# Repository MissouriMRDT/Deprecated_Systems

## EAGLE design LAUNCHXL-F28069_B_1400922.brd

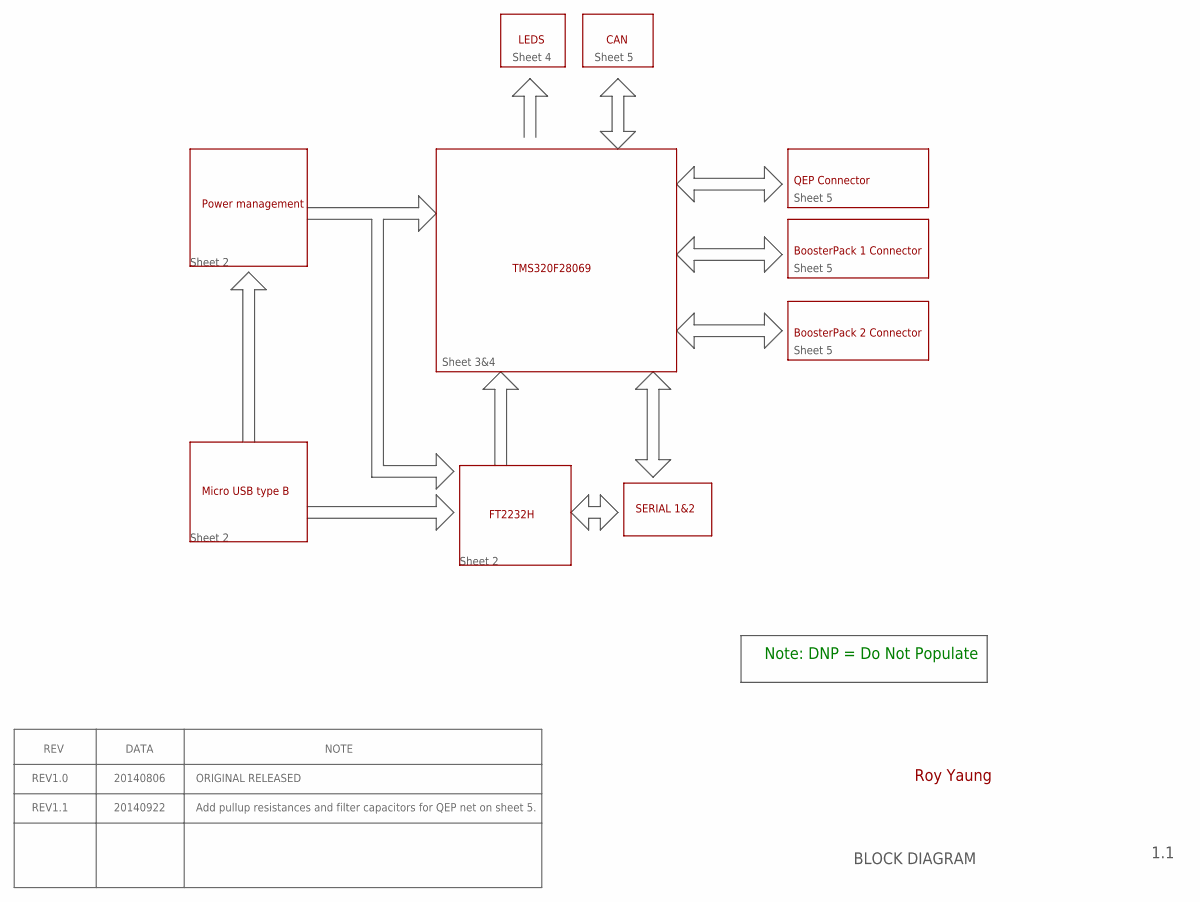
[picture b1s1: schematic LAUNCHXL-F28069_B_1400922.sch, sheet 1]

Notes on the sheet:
1.1
BLOCK DIAGRAM
Power management
Micro USB type B
FT2232H
TMS320F28069
BoosterPack 1 Connector
LEDS
CAN
SERIAL 1&2
Sheet 2
Sheet 3&4
BoosterPack 2 Connector
QEP Connector
Note: DNP = Do Not Populate
Roy Yaung
Sheet 5
Sheet 4
REV
DATA
NOTE
REV1.0
REV1.1
20140806
20140922
ORIGINAL RELEASED
Add pullup resistances and filter capacitors for QEP net on sheet 5.

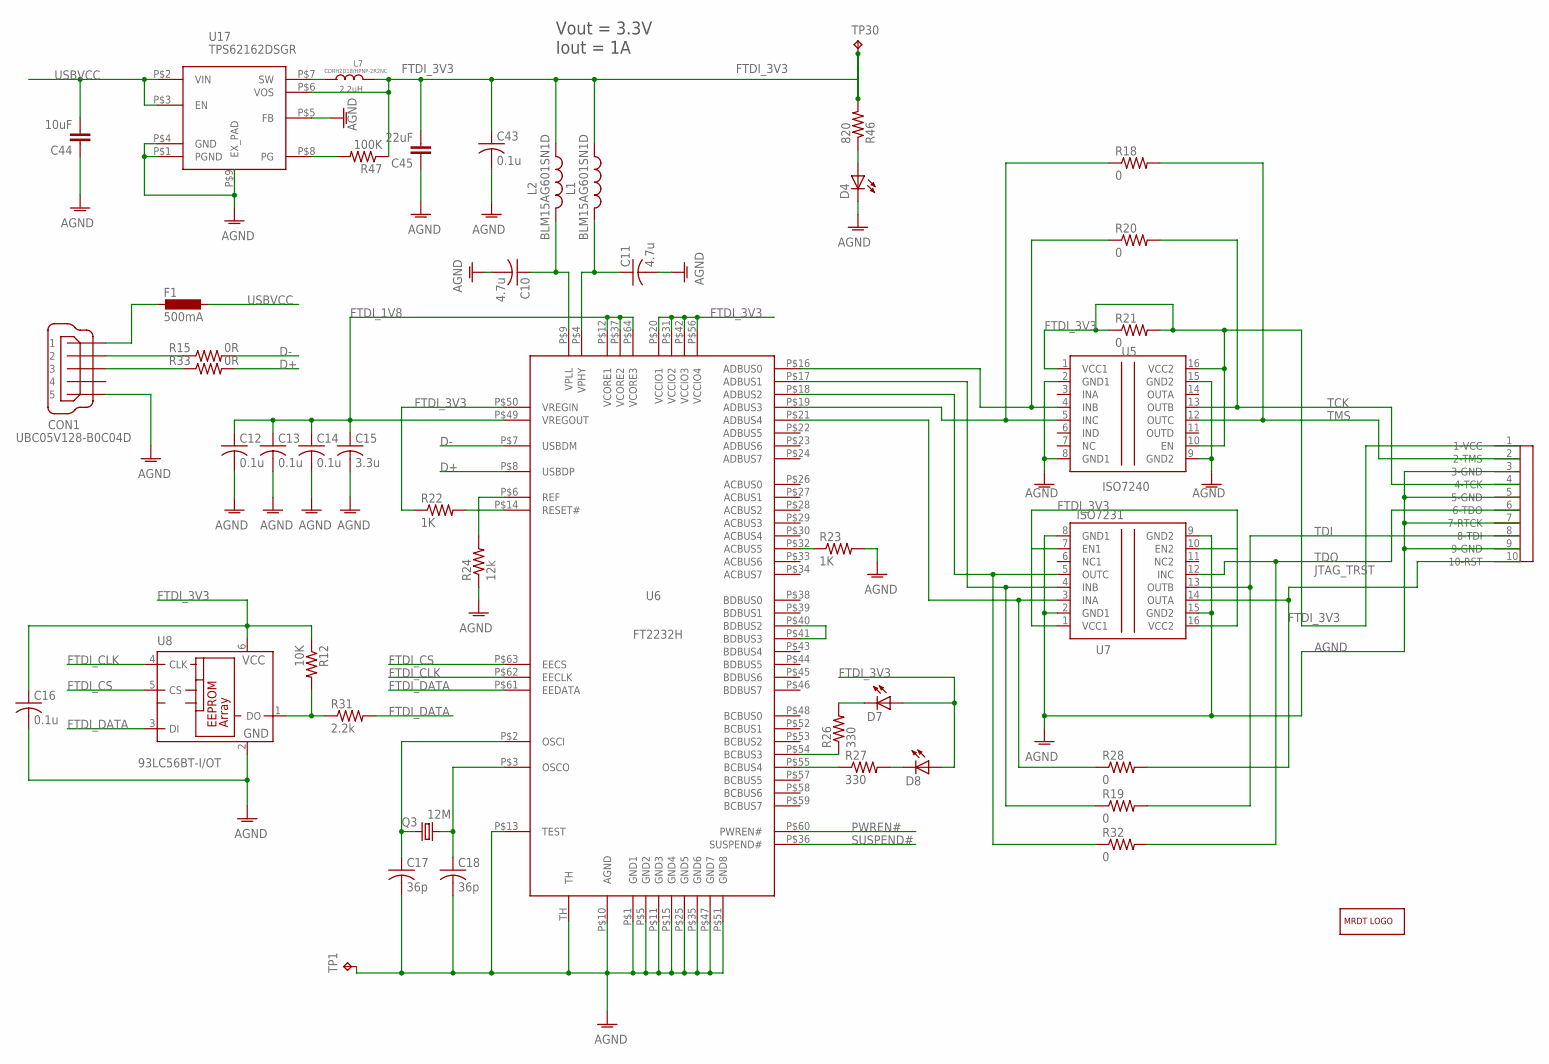
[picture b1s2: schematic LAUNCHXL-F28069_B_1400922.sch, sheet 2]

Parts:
C10, C11: 4.7u; C0402
C12, C13, C14, C16, C43: 0.1u; C0402
C15: 3.3u; C0402
C17, C18: 36p; C0402
C44: 10uF; SPARKFUN_1210
C45: 22uF; SPARKFUN_1210
CON1: UBC05V128-B0C04D; 32005-201
D4, D7, D8: LEDCHIP-LED0603; CHIP-LED0603
F1: 500mA; L1812
L1, L2: BLM15AG601SN1D; R0402
L7: 2.2uH; INDUCT-3.2*3.2
LOGO1: MRDT_LOGO
Q3: 12M; HC49UP
R12: 10K; R0402
R15, R33: 0R; R0402
R18, R19, R20, R21, R28, R32: 0; R1206
R22, R23: 1K; R0402
R24: 12k; R0402
R26, R27: 330; R0402
R31: 2.2k; R0402
R46: 820; R0402
R47: 100K; R0402
TP1, TP30: TESTPAD_TPB1,27; TESTPAD_B1,27
U5: ISO7240; SO-16DW
U6: FT2232H; QFN64
U7: ISO7231; SO-16DW
U8: 93LC56BT-I/OT; SOT23-6
U17: TPS62162DSGR; TI_DSG8
U$1: 1175-1733-ND; 1.27MM_2X5_BOX_HEADER_STRAIGHT

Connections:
AGND: C10.2, C11.2, C12.2, C13.2, C14.2, C15.2, C16.2, C17.2, C18.2, C43.2, C44.1, C45.1, CON1.5, D4.C, R23.2, R24.1, TP1.TP, U5.2 (GND1), U5.8 (GND1), U5.9 (GND2), U5.15 (GND2), U6.P$1 (GND1), U6.P$5 (GND2), U6.P$10 (AGND), U6.P$11 (GND3), U6.P$13 (TEST), U6.P$15 (GND4), U6.P$25 (GND5), U6.P$35 (GND6), U6.P$47 (GND7), U6.P$51 (GND8), U6.TH, U7.2 (GND1), U7.8 (GND1), U7.9 (GND2), U7.15 (GND2), U8.2 (GND), U17.P$1 (PGND), U17.P$4 (GND), U17.P$5 (FB), U17.P$9 (EX_PAD), U$1.3 (3-GND), U$1.5 (5-GND), U$1.7 (7-RTCK), U$1.9 (9-GND); also elsewhere on the board
D+: R33.2, U6.P$8 (USBDP)
D-: R15.2, U6.P$7 (USBDM)
FTDI_1V8: C12.1, C13.1, C14.1, C15.1, U6.P$12 (VCORE1), U6.P$37 (VCORE2), U6.P$49 (VREGOUT), U6.P$64 (VCORE3)
FTDI_3V3: C16.1, C43.1, C45.2, D7.A, D8.A, L1.1, L2.1, L7.P$1 (1), R12.1, R21.1, R21.2, R22.1, R46.2, R47.1, TP30.TP, U5.1 (VCC1), U5.10 (EN), U5.16 (VCC2), U6.P$20 (VCCIO1), U6.P$31 (VCCIO2), U6.P$42 (VCCIO3), U6.P$50 (VREGIN), U6.P$56 (VCCIO4), U7.1 (VCC1), U7.7 (EN1), U7.10 (EN2), U7.16 (VCC2), U8.6 (VCC), U17.P$6 (VOS), U$1.1 (1-VCC); also elsewhere on the board
FTDI_CLK: U6.P$62 (EECLK), U8.4 (CLK)
FTDI_CS: U6.P$63 (EECS), U8.5 (CS)
FTDI_DATA: R31.2, U6.P$61 (EEDATA), U8.3 (DI)
JTAG_TRST: R28.2, U7.14 (OUTA), U$1.10 (10-RST)
unnamed: R20.1, U5.4 (INB), U6.P$16 (ADBUS0)
unnamed: C17.1, Q3.1, U6.P$2 (OSCI)
unnamed: R19.1, U6.P$17 (ADBUS1), U7.4 (INB)
unnamed: R32.1, U6.P$18 (ADBUS2), U7.5 (OUTC)
unnamed: R18.1, U5.5 (INC), U6.P$19 (ADBUS3)
unnamed: C18.1, Q3.2, U6.P$3 (OSCO)
unnamed: R12.2, R31.1, U8.1 (DO)
unnamed: R28.1, U6.P$21 (ADBUS4), U7.3 (INA)
unnamed: R23.1, U6.P$32 (ACBUS5)
unnamed: U6.P$40 (BDBUS2), U6.P$41 (BDBUS3)
unnamed: R24.2, U6.P$6 (REF)
unnamed: R26.1, U6.P$54 (BCBUS3)
unnamed: C11.1, L1.2, U6.P$4 (VPHY)
unnamed: R27.1, U6.P$55 (BCBUS4)
unnamed: D7.C, R26.2
unnamed: D8.C, R27.2
unnamed: C10.1, L2.2, U6.P$9 (VPLL)
unnamed: R22.2, U6.P$14 (RESET#)
unnamed: CON1.2, R15.1
unnamed: CON1.3, R33.1
unnamed: D4.A, R46.1
unnamed: R47.2, U17.P$8 (PG)
unnamed: L7.P$2 (2), U17.P$7 (SW)
PWREN#: U6.P$60 (PWREN#)
SUSPEND#: U6.P$36 (SUSPEND#)
TCK: R20.2, U5.13 (OUTB), U$1.4 (4-TCK)
TDI: R19.2, U7.13 (OUTB), U$1.8 (8-TDI)
TDO: R32.2, U7.12 (INC), U$1.6 (6-TDO)
TMS: R18.2, U5.12 (OUTC), U$1.2 (2-TMS)
USBVCC: C44.2, F1.1, U17.P$2 (VIN), U17.P$3 (EN)
XUSB: CON1.1, F1.2

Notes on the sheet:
Vout = 3.3V
Iout = 1A
CDRH2D18/HPNP-2R2NC

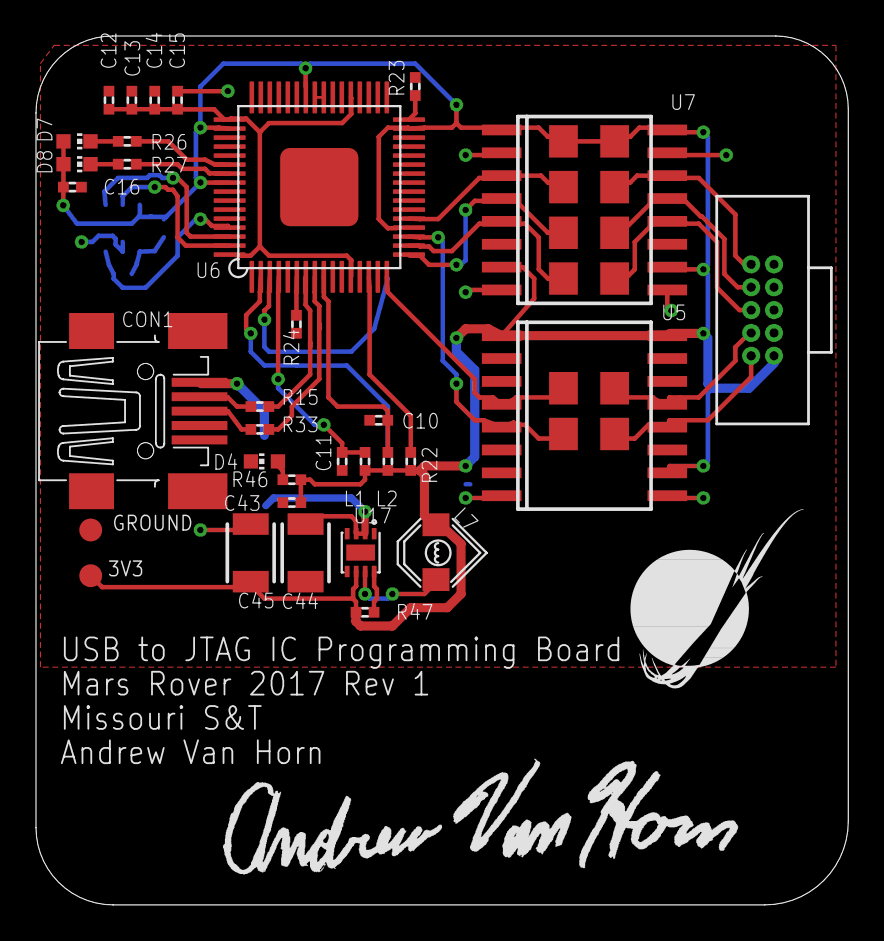
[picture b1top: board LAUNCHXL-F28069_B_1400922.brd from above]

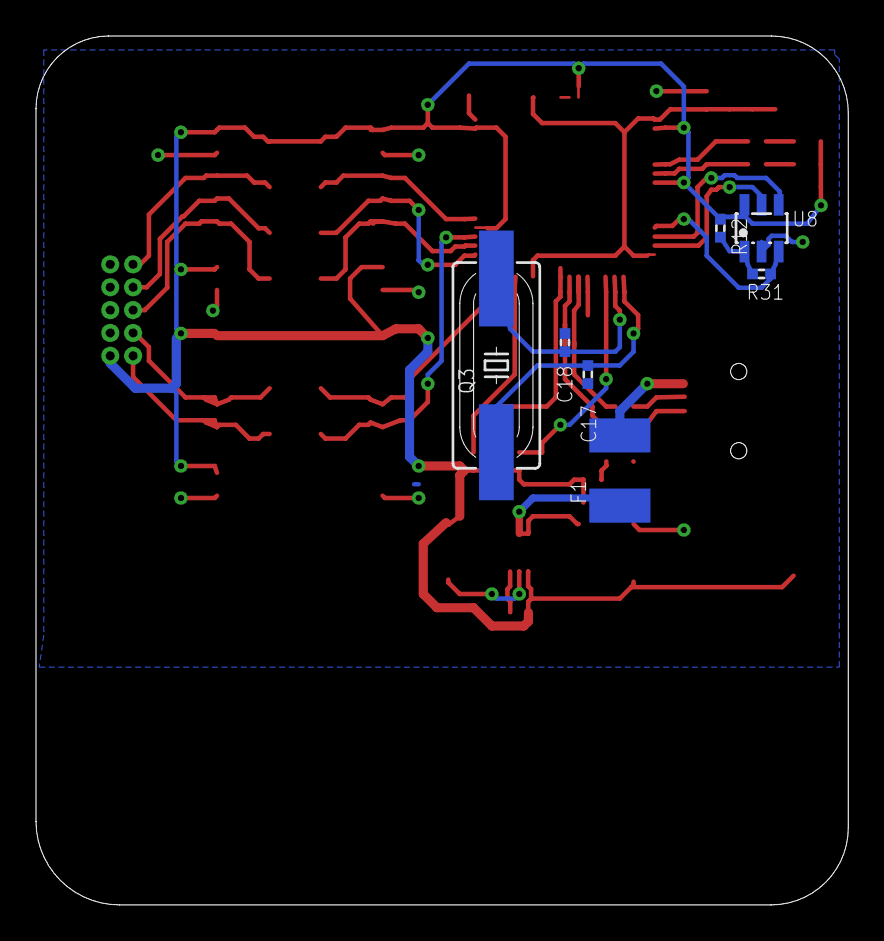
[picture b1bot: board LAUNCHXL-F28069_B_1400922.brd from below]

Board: 2 copper layers, 45.1 x 48.3 mm, 48 parts (7 on the bottom side), 38 nets.

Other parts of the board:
3V3: TESTPAD_TPB1,27; TESTPAD_B1,27
GROUND: TESTPAD_TPB1,27; TESTPAD_B1,27
U$2: ANDREW_VAN_HORN_SIGNATURE

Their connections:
AGND: GROUND.TP; also elsewhere on the board
FTDI_3V3: 3V3.TP; also elsewhere on the board

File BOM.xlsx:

Part | Value | Device | Package | Description | MF | MPN | OC_FARNELL | OC_NEWARK | TP_SIGNAL_NAME
3V3 | TESTPAD_TPB1,27 | TESTPAD_TPB1,27 | TESTPAD_B1,27 | Test pad
C10 | 4.7u | C-USC0402 | C0402 | CAPACITOR, American symbol
C11 | 4.7u | C-USC0402 | C0402 | CAPACITOR, American symbol
C12 | 0.1u | C-USC0402 | C0402 | CAPACITOR, American symbol
C13 | 0.1u | C-USC0402 | C0402 | CAPACITOR, American symbol
C14 | 0.1u | C-USC0402 | C0402 | CAPACITOR, American symbol
C15 | 3.3u | C-USC0402 | C0402 | CAPACITOR, American symbol
C16 | 0.1u | C-USC0402 | C0402 | CAPACITOR, American symbol
C17 | 36p | C-USC0402 | C0402 | CAPACITOR, American symbol
C18 | 36p | C-USC0402 | C0402 | CAPACITOR, American symbol
C43 | 0.1u | C-USC0402 | C0402 | CAPACITOR, American symbol
C44 | 10uF | SPARKFUN_CAP1210 | SPARKFUN_1210 | Capacitor
C45 | 22uF | SPARKFUN_CAP1210 | SPARKFUN_1210 | Capacitor
CON1 | UBC05V128-B0C04D | MINI-USB-32005-201 | 32005-201 | MINI USB-B Conector |  |  | unknown | unknown
D4 |  | LEDCHIP-LED0603 | CHIP-LED0603 | LED
D7 |  | LEDCHIP-LED0603 | CHIP-LED0603 | LED
D8 |  | LEDCHIP-LED0603 | CHIP-LED0603 | LED
F1 | 500mA | L-EUL1812 | L1812 | INDUCTOR, European symbol
GROUND | TESTPAD_TPB1,27 | TESTPAD_TPB1,27 | TESTPAD_B1,27 | Test pad
L1 | BLM15AG601SN1D | L-US0402 | R0402 | INDUCTOR, American symbol
L2 | BLM15AG601SN1D | L-US0402 | R0402 | INDUCTOR, American symbol
L7 | 2.2uH | VLF4012A` | INDUCT-3.2*3.2
Q3 | 12M | CRYSTALHC49UP | HC49UP | CRYSTAL |  |  | unknown | unknown
R12 | 10K | R-US_R0402 | R0402 | RESISTOR, American symbol
R15 | 0R | R-US_R0402 | R0402 | RESISTOR, American symbol
R18 | 0 | R-US_R1206 | R1206 | RESISTOR, American symbol
R19 | 0 | R-US_R1206 | R1206 | RESISTOR, American symbol
R20 | 0 | R-US_R1206 | R1206 | RESISTOR, American symbol
R21 | 0 | R-US_R1206 | R1206 | RESISTOR, American symbol
R22 | 1K | R-US_R0402 | R0402 | RESISTOR, American symbol
R23 | 1K | R-US_R0402 | R0402 | RESISTOR, American symbol
R24 | 12k | R-US_R0402 | R0402 | RESISTOR, American symbol
R26 | 330 | R-US_R0402 | R0402 | RESISTOR, American symbol
R27 | 330 | R-US_R0402 | R0402 | RESISTOR, American symbol
R28 | 0 | R-US_R1206 | R1206 | RESISTOR, American symbol
R31 | 2.2k | R-US_R0402 | R0402 | RESISTOR, American symbol
R32 | 0 | R-US_R1206 | R1206 | RESISTOR, American symbol
R33 | 0R | R-US_R0402 | R0402 | RESISTOR, American symbol
R46 | 820 | R-US_R0402 | R0402 | RESISTOR, American symbol
R47 | 100K | R-US_R0402 | R0402 | RESISTOR, American symbol
U$1 | 1175-1733-ND | 1175-1733-ND | 1.27MM_2X5_BOX_HEADER_STRAIGHT
U5 | ISO7240 | ISO7240 | SO-16DW | HIGH SPEED QUAD DIGITAL ISOLATORS |  | ISO7240MDW | 1755124 | 58M0385
U6 | FT2232H | FT2232H | QFN64
U7 | ISO7231 | ISO7231 | SO-16DW
U8 | 93LC56BT-I/OT | 93 | SOT23-6 | Serial EPROM
U17 | TPS62162DSGR | TPS62162DSGR | TI_DSG8

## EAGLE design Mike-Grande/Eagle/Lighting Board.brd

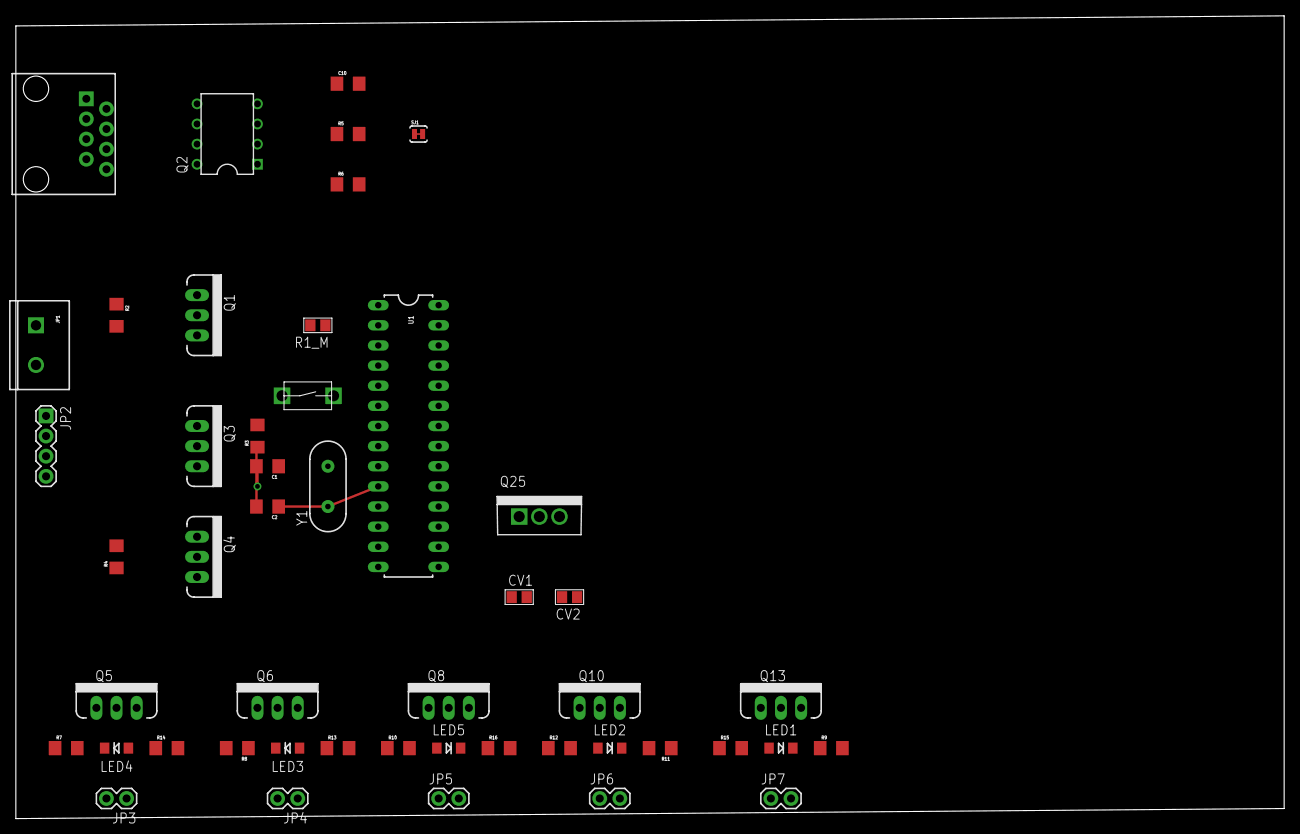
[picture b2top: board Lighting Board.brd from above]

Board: 2 copper layers, 160.0 x 101.3 mm, 48 parts (0 on the bottom side), 34 nets.

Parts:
C1, C2: 0.1uF; 1206
C10: .1uF; 1206
CV1, CV2: C_0805
JP1: M025MM; SCREWTERMINAL-5MM-2
JP2: 1X04
JP3, JP4, JP5, JP6, JP7: M02PTH; 1X02
LED1, LED2, LED3, LED4, LED5: LED-1206
MS: J_MC32857; J_TOGGLE
Q1, Q3, Q4, Q5, Q6, Q8, Q10, Q13: MOSFET-NCHANNELFQP30N06L; TO220V
Q2: Q_LTC490; DIP8
Q25: LDO; TO-220
R1_M: 200; R_0805
R2, R3, R4, R7, R8, R10, R12, R15: 1k; 1206
R5, R6: 120 Ohm; 1206
R9, R11: 1206
R13, R14, R16: 200; 1206
SJ1: SOLDERJUMPERTRACE; SJ_2S-TRACE
U1: ATMEGA328P_PDIP; DIL28-3
U$1: RJ45-8PTH; RJ45-8
Y1: HC49US

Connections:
D1: Q10.1, R12.2, U1.13
D2: Q13.1, R15.2, U1.14
GND: C1.2, C2.2, C10.2, CV1.2, CV2.2, JP1.2, MS.P$1, Q1.3, Q2.4, Q3.3, Q4.3, Q5.3, Q6.3, Q8.3, Q10.3, Q13.3, Q25.2, R2.1, R3.1, R4.1, R7.1, R8.1, R10.1, R12.1, R15.1, SJ1.1, U1.8, U1.22
unnamed: Q2.5, R6.2, U$1.1
unnamed: C2.1, U1.10, Y1.1
unnamed: LED1.A, R9.1
unnamed: LED2.A, R11.1
unnamed: LED3.A, R13.1
unnamed: LED4.A, R14.1
unnamed: LED5.A, R16.1
unnamed: Q2.6, R6.1, U$1.2
unnamed: Q2.7, R5.2, U$1.6
unnamed: Q2.8, R5.1, U$1.3
unnamed: SJ1.2, U$1.7, U$1.8
unnamed: C1.1, U1.9, Y1.2
unnamed: JP2.2, Q1.2
unnamed: JP2.3, Q3.2
unnamed: JP2.4, Q4.2
unnamed: MS.P$2, R1_M.1, U1.1
N%2: JP4.2, LED3.C, Q6.2
N%3: JP3.2, LED4.C, Q5.2
N%106: JP5.2, LED5.C, Q8.2
N%107: JP6.2, LED2.C, Q10.2
N%110: JP7.2, LED1.C, Q13.2
PWM1: Q3.1, R3.2, U1.5
PWM2: Q4.1, R4.2, U1.11
PWM3: Q1.1, R2.2, U1.12
PWM4: Q5.1, R7.2, U1.15
PWM5: Q6.1, R8.2, U1.16
PWM6: Q8.1, R10.2, U1.17
RXD: Q2.2, U1.2
TXD: Q2.3, U1.3
V5: C10.1, CV2.1, Q2.1, Q25.3, R1_M.2, U1.7, U1.20
VIN: CV1.1, JP1.1, JP2.1, JP3.1, JP4.1, JP5.1, JP6.1, JP7.1, Q25.1, R9.2, R11.2, R13.2, R14.2, R16.2

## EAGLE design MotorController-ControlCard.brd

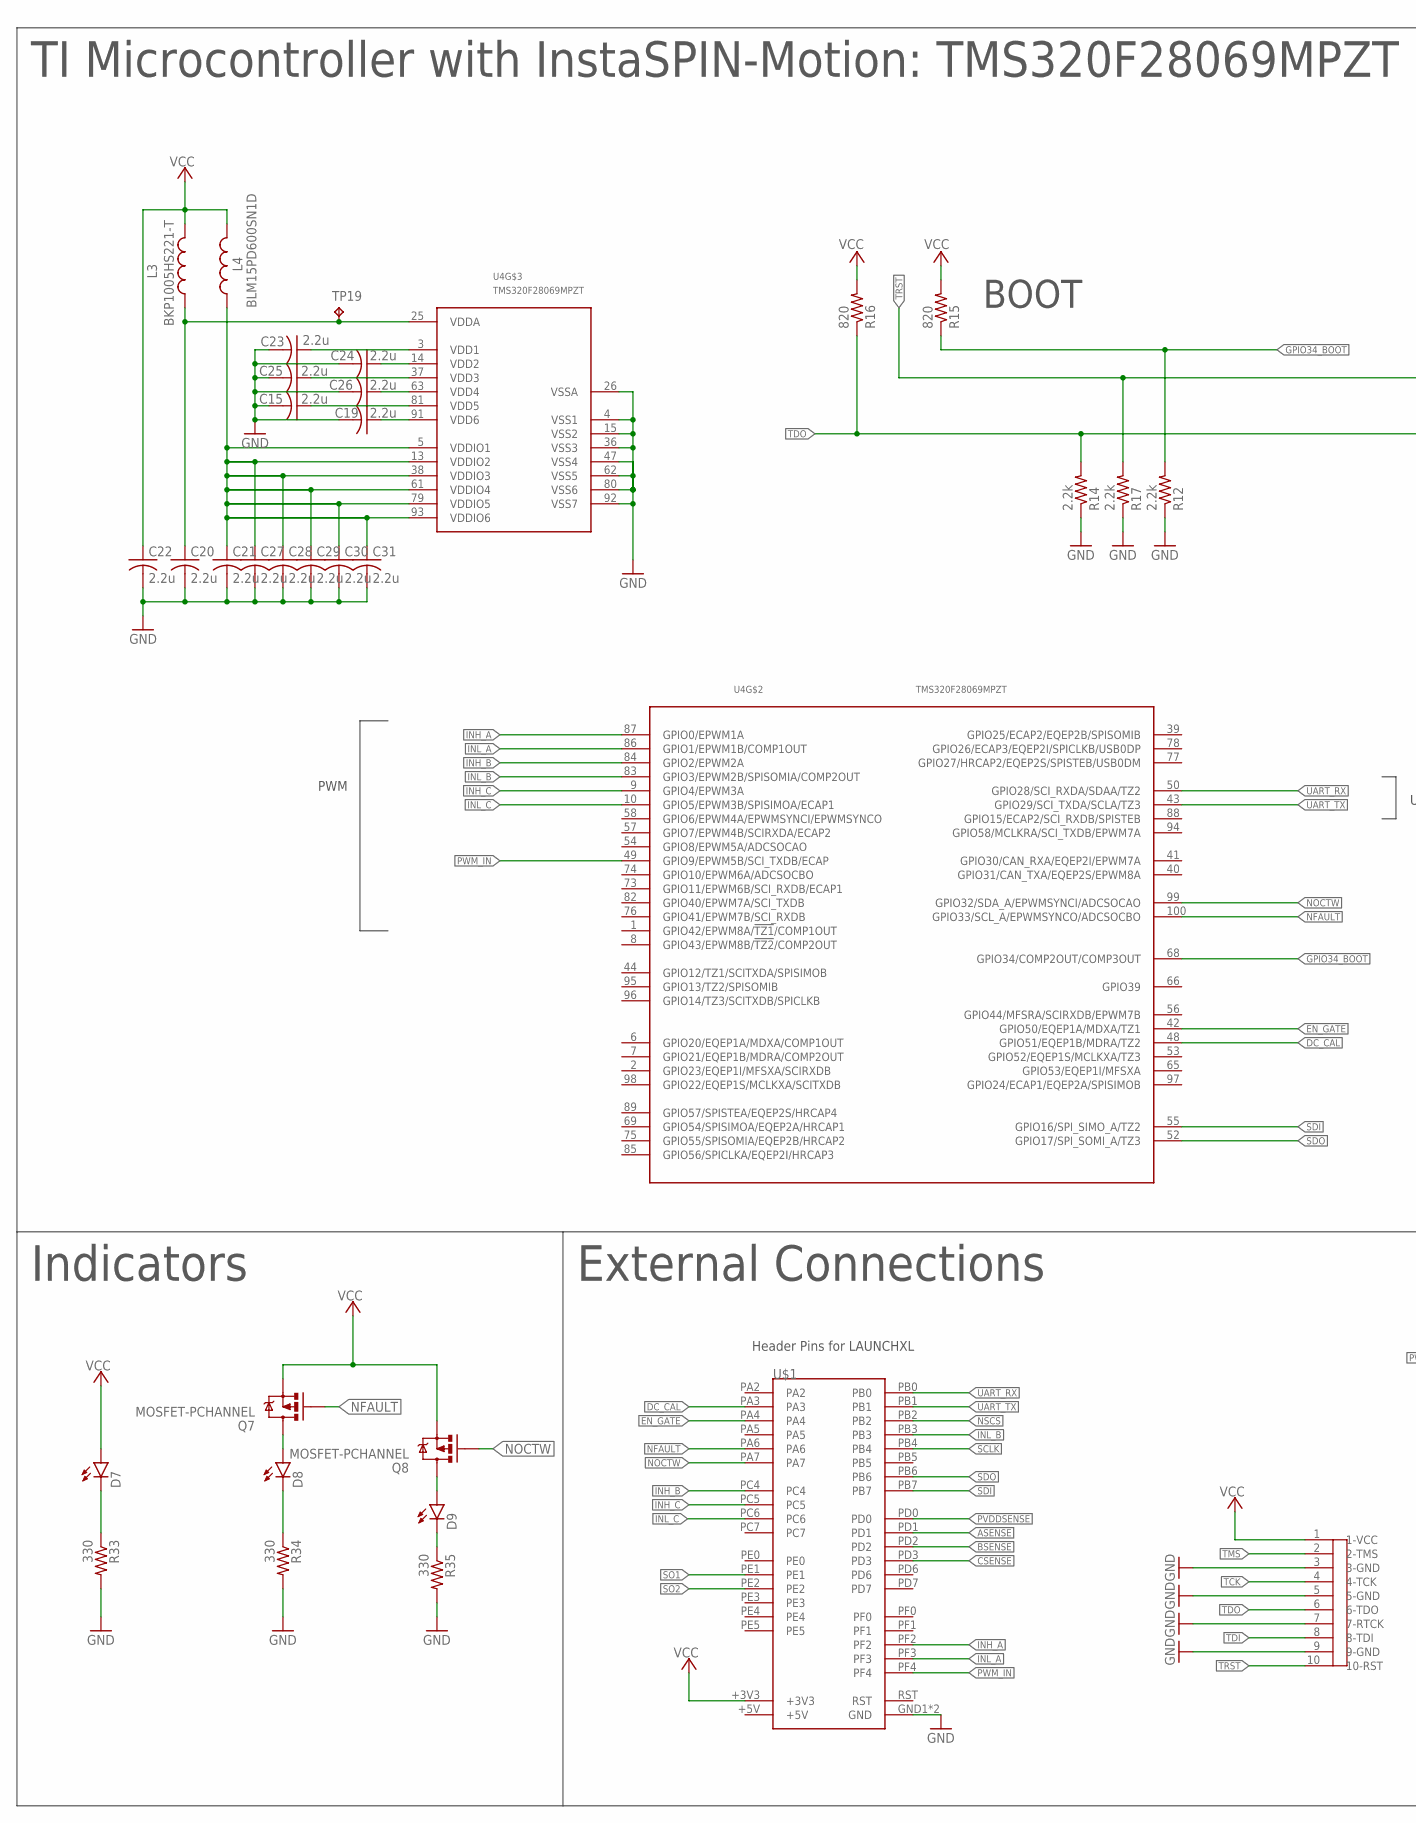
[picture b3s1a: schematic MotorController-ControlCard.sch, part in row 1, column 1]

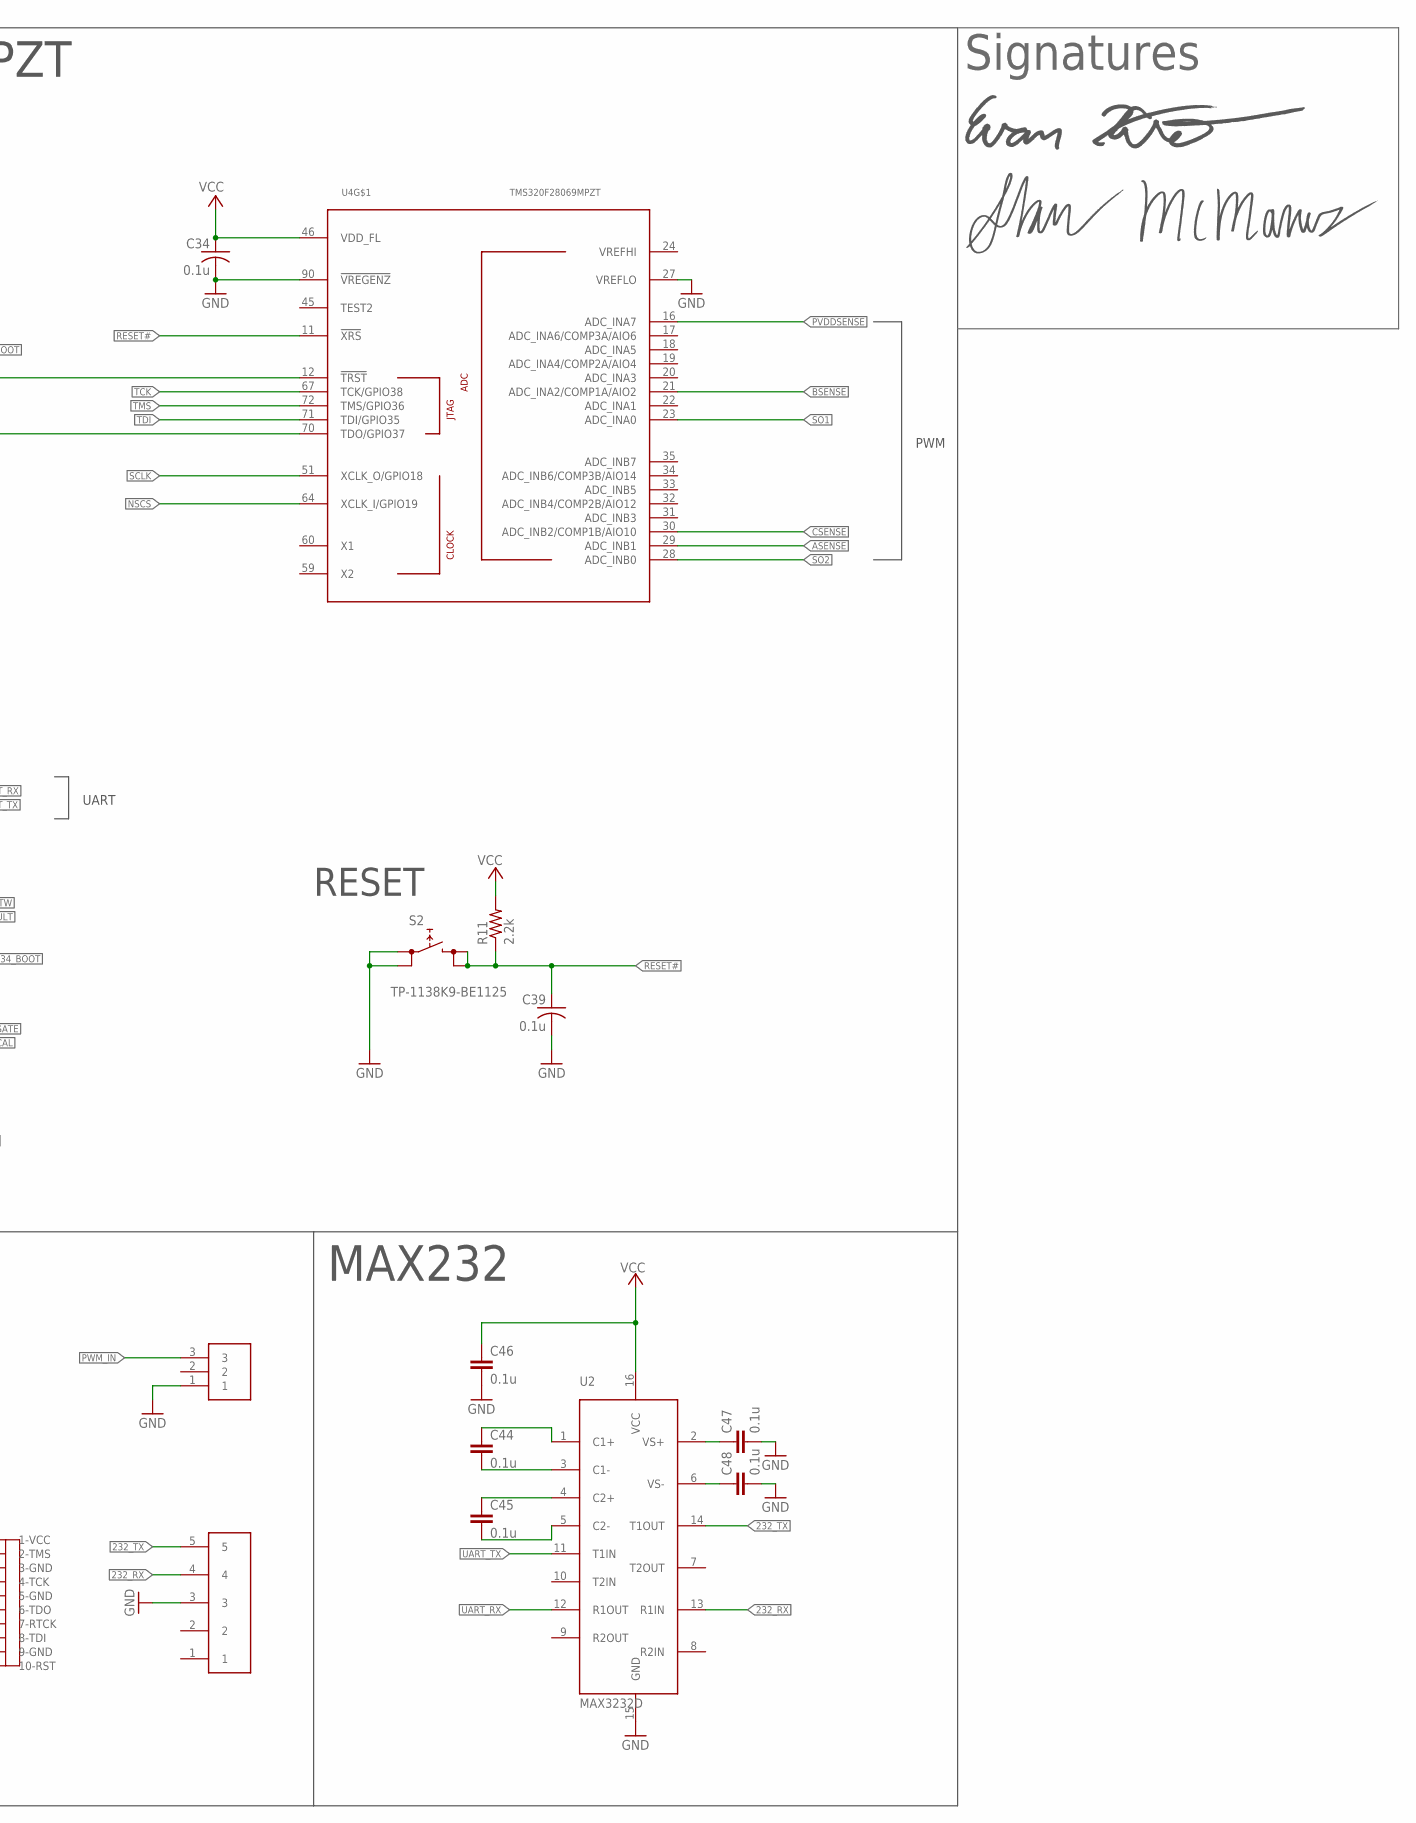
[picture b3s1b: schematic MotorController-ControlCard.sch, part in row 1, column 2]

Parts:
C15, C19, C20, C21, C22, C23, C24, C25, C26, C27, C28, C29, C30, C31: 2.2u; C0402
C34, C39: 0.1u; C0402
C44, C45, C46, C47, C48: 0.1u; 0805
D7, D8, D9: LED1206; LED-1206
J2: SL03THROUGH_HOLE; MOLEX_SL_03_TH
L3: BKP1005HS221-T; R0402
L4: BLM15PD600SN1D; R0402
Q7, Q8: MOSFET-PCHANNEL; SOT23-3
R11, R12, R14, R17: 2.2k; R0402
R15, R16: 820; R0402
R33, R34, R35: 330; 0805
S2: TP-1138K9-BE1125; FSMJSMA
TP19: TESTPAD_TPB1,27; TESTPAD_B1,27
U2: MAX3232D; SOIC16
U4: TMS320F28069MPZT; PQFP100
U$1: TIVA-123; TIVA-C
U$2: IDC_BOX_HEADER_2X5_1.27MM; 1.27MM_2X5_BOX_HEADER_STRAIGHT
U$3: EVAN_HITE_SIGNATURE
U$4: 5PIN
U$5: SHAUN_MCMANUS_SIGNATURE

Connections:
232_RX: U2.13 (R1IN), U$4.4
232_TX: U2.14 (T1OUT), U$4.5
+3V3: C22.1, C34.1, C46.1, D7.A, L3.2, L4.2, Q7.2 (S), Q8.2 (S), R11.2, R15.2, R16.2, U2.16 (VCC), U4.46 (VDD_FL), U$1.+3V3, U$2.1 (1-VCC)
+5V: U$1.+5V
ASENSE: U4.29 (ADC_INB1), U$1.PD1
BSENSE: U4.21 (ADC_INA2/COMP1A/AIO2), U$1.PD2
CSENSE: U4.30 (ADC_INB2/COMP1B/AIO10), U$1.PD3
DC_CAL: U4.48 (GPIO51/EQEP1B/MDRA/TZ2), U$1.PA3
EN_GATE: U4.42 (GPIO50/EQEP1A/MDXA/TZ1), U$1.PA4
GND: C15.2, C19.2, C20.2, C21.2, C22.2, C23.2, C24.2, C25.2, C26.2, C27.2, C28.2, C29.2, C30.2, C31.2, C34.2, C39.2, C46.2, C47.2, C48.2, J2.1, R12.1, R14.1, R17.1, R33.2, R34.2, R35.2, S2.P$1 (0), S2.P$2 (0), U2.15 (GND), U4.4 (VSS1), U4.15 (VSS2), U4.26 (VSSA), U4.27 (VREFLO), U4.36 (VSS3), U4.47 (VSS4), U4.62 (VSS5), U4.80 (VSS6), U4.90 (!VREGENZ), U4.92 (VSS7), U$1.GND1 (GND), U$1.GND2 (GND), U$2.3 (3-GND), U$2.5 (5-GND), U$2.7 (7-RTCK), U$2.9 (9-GND), U$4.3
GPIO34_BOOT: R12.2, R15.1, U4.68 (GPIO34/COMP2OUT/COMP3OUT)
INH_A: U4.87 (GPIO0/EPWM1A), U$1.PF2
INH_B: U4.84 (GPIO2/EPWM2A), U$1.PC4
INH_C: U4.9 (GPIO4/EPWM3A), U$1.PC5
INL_A: U4.86 (GPIO1/EPWM1B/COMP1OUT), U$1.PF3
INL_B: U4.83 (GPIO3/EPWM2B/SPISOMIA/COMP2OUT), U$1.PB3
INL_C: U4.10 (GPIO5/EPWM3B/SPISIMOA/ECAP1), U$1.PC6
unnamed: C23.1, U4.3 (VDD1)
unnamed: C24.1, U4.14 (VDD2)
unnamed: C25.1, U4.37 (VDD3)
unnamed: C26.1, U4.63 (VDD4)
unnamed: C15.1, U4.81 (VDD5)
unnamed: D7.C, R33.1
unnamed: D8.C, R34.1
unnamed: D9.C, R35.1
unnamed: D9.A, Q8.3 (D)
unnamed: D8.A, Q7.3 (D)
unnamed: C19.1, U4.91 (VDD6)
unnamed: C44.1, U2.1 (C1+)
unnamed: C44.2, U2.3 (C1-)
unnamed: C45.1, U2.4 (C2+)
unnamed: C45.2, U2.5 (C2-)
unnamed: C48.1, U2.6 (VS-)
unnamed: C47.1, U2.2 (VS+)
NFAULT: Q7.1 (G), U4.100 (GPIO33/SCL_A/EPWMSYNCO/ADCSOCBO), U$1.PA6
NOCTW: Q8.1 (G), U4.99 (GPIO32/SDA_A/EPWMSYNCI/ADCSOCAO), U$1.PA7
NSCS: U4.64 (XCLK_I/GPIO19), U$1.PB2
PVDDSENSE: U4.16 (ADC_INA7), U$1.PD0
PWM_IN: J2.3, U4.49 (GPIO9/EPWM5B/SCI_TXDB/ECAP), U$1.PF4
RESET#: C39.1, R11.1, S2.P$3 (1), S2.P$4 (1), U4.11 (!XRS)
RST: U$1.RST
SCLK: U4.51 (XCLK_O/GPIO18), U$1.PB4
SDI: U4.55 (GPIO16/SPI_SIMO_A/TZ2), U$1.PB7
SDO: U4.52 (GPIO17/SPI_SOMI_A/TZ3), U$1.PB6
SO1: U4.23 (ADC_INA0), U$1.PE1
SO2: U4.28 (ADC_INB0), U$1.PE2
TCK: U4.67 (TCK/GPIO38), U$2.4 (4-TCK)
TDI: U4.71 (TDI/GPIO35), U$2.8 (8-TDI)
TDO: R14.2, R16.1, U4.70 (TDO/GPIO37), U$2.6 (6-TDO)
TMS: U4.72 (TMS/GPIO36), U$2.2 (2-TMS)
TRST: R17.2, U4.12 (!TRST), U$2.10 (10-RST)
UART_RX: U2.12 (R1OUT), U4.50 (GPIO28/SCI_RXDA/SDAA/TZ2), U$1.PB0
UART_TX: U2.11 (T1IN), U4.43 (GPIO29/SCI_TXDA/SCLA/TZ3), U$1.PB1
VDDA: C20.1, L3.1, TP19.TP, U4.25 (VDDA)
VDDIO: C21.1, C27.1, C28.1, C29.1, C30.1, C31.1, L4.1, U4.5 (VDDIO1), U4.13 (VDDIO2), U4.38 (VDDIO3), U4.61 (VDDIO4), U4.79 (VDDIO5), U4.93 (VDDIO6)

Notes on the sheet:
PWM
UART
RESET
TI Microcontroller with InstaSPIN-Motion: TMS320F28069MPZT
Indicators
External Connections
BOOT
MAX232
Header Pins for LAUNCHXL
Signatures

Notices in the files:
parts and their libraries:
SparkFun-DigitalIC: Licensing: CC v3.0 Share-Alike You are welcome to use this library for commercial purposes.
LilyPad-Wearables: Licensing:Creative Commons ShareAlike 4.0 International - https://creativecommons.org/licenses/by-sa/4.0
